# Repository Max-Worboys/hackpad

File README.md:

# ETCPAD / HackPad

ETCPAD is an 8 key macropad designed for use with the ETC Nomad lighting control software

## CAD Model:
Everything fits together using 4 3mm Dowels

It has 2 separate printed pieces, the bottom which houses the PCB and the top which as holes for the keycaps
Made in Fusion360.

*Green Block = PCB

## PCB
Here's my PCB! It was made in KiCad.
Schematic

PCB

## BOM:
Here is be everything you need to make this hackpad

- 8x Cherry MX Switches
- 8x DSA Keycaps
- 1x XIAO RP2040
- 1x Case (2 x 3D printed parts)

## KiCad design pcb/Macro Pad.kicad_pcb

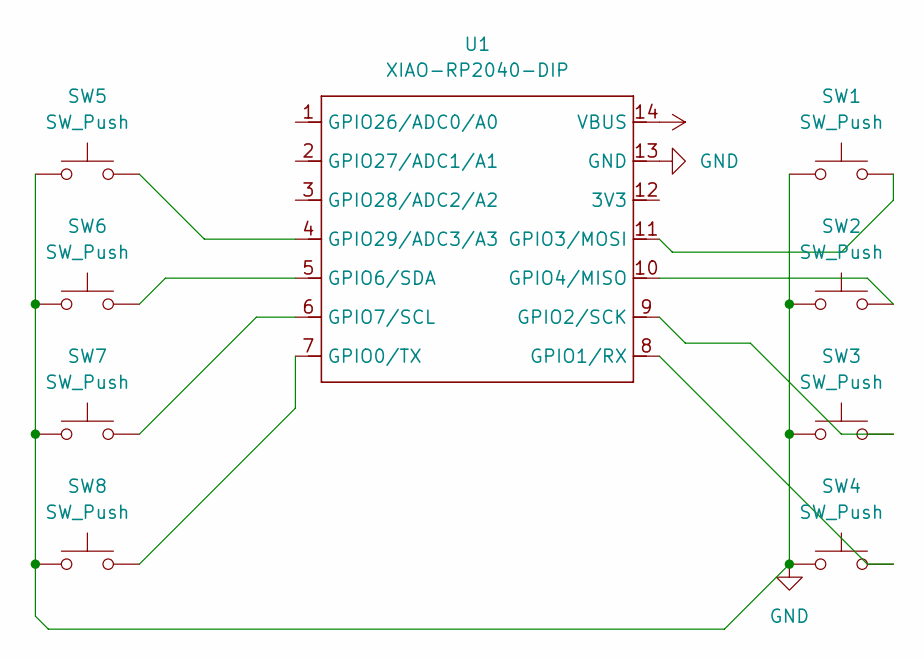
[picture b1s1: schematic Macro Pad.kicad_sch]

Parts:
SW1, SW2, SW3, SW4, SW5, SW6, SW7, SW8: SW_Push; SW_Cherry_MX_1.00u_PCB
U1: XIAO-RP2040-DIP

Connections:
+5V: U1.14 (VBUS)
GND: SW1.2, SW2.2, SW3.2, SW4.2, SW5.2, SW6.2, SW7.2, SW8.2, U1.13 (GND)
unnamed: SW8.1, U1.7 (GPIO0/TX)
unnamed: SW4.1, U1.8 (GPIO1/RX)
unnamed: SW3.1, U1.9 (GPIO2/SCK)
unnamed: SW1.1, U1.11 (GPIO3/MOSI)
unnamed: SW2.1, U1.10 (GPIO4/MISO)
unnamed: SW6.1, U1.5 (GPIO6/SDA)
unnamed: SW7.1, U1.6 (GPIO7/SCL)
unnamed: SW5.1, U1.4 (GPIO29/ADC3/A3)

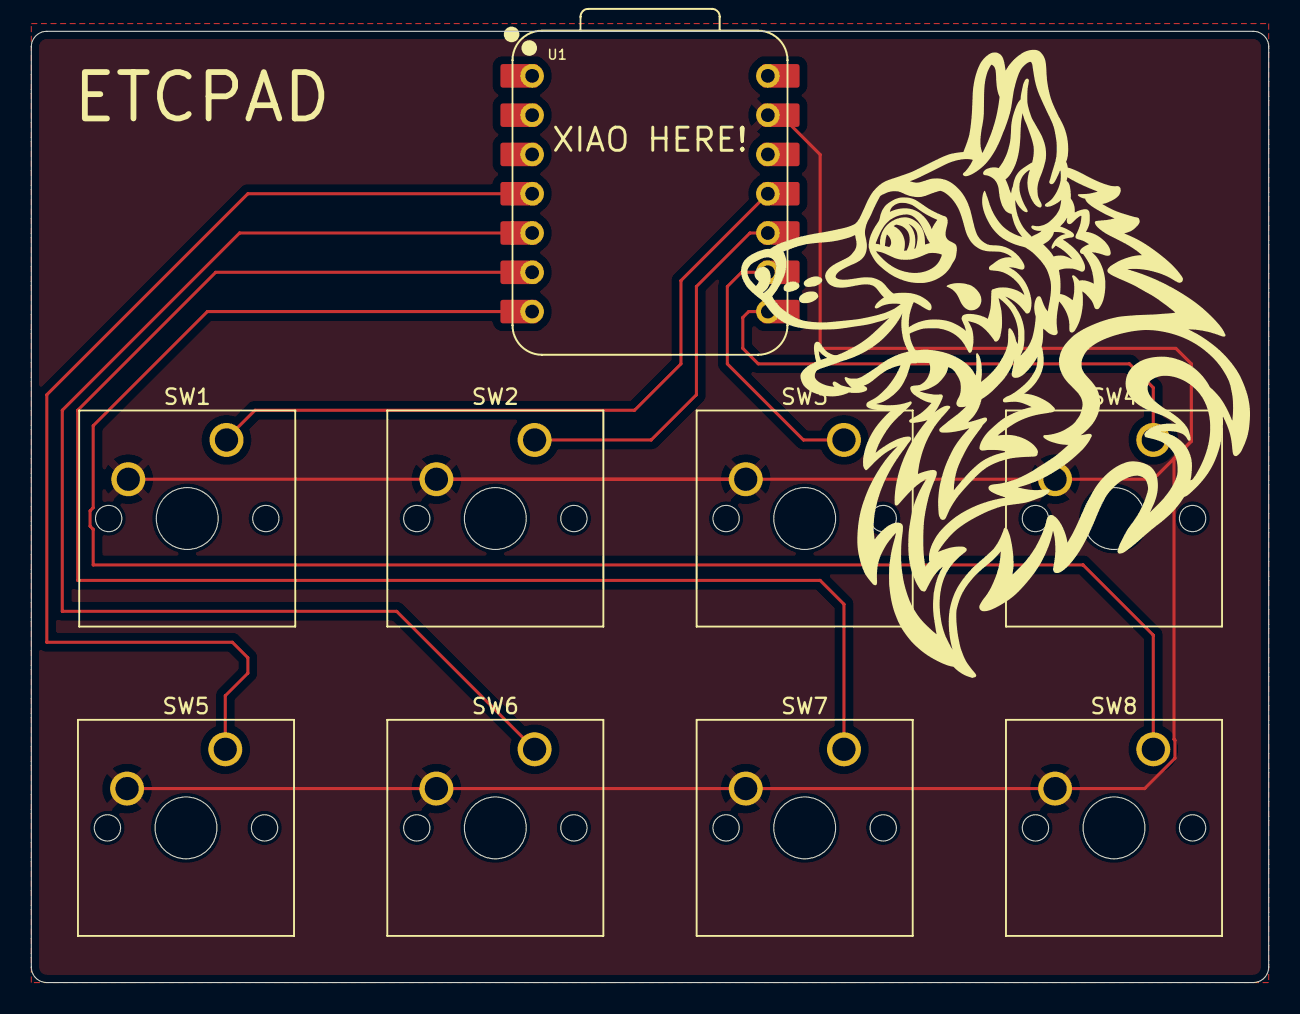
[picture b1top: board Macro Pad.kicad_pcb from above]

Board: 2 copper layers, 80.0 x 61.5 mm, 9 parts (0 on the bottom side), 9 nets.

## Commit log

2025-05-30 Rename Screenshot 2025-05-30 212137.png to Overall.png
2025-05-30 Rename Screenshot 2025-05-30 212316.png to Split-Case.png
2025-05-30 Rename Screenshot from 2025-05-30 19-58-51.png to PCB.png
2025-05-30 Rename Screenshot from 2025-05-30 21-30-41.png to Schematic.png
